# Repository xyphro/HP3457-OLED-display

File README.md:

# HP3457-OLED-display
A modern replacement for the low contrast HP3457 Multimeter LCD

HP3457 is a great multimeter of the pre Keysight and pre Agilent era from HP.
If you do some research on it, you get to learn a lot of details of how much nice engineering work has been put into the development of this multimeter. It is certainly one of the things, that was developed by great experienced engineers and is a masterpiece in finding proper solutions for technical challenges to push accuracy but also measurement speed on the right level.

HOWEVER: The display is crap. It is a low contrast display with small characters and extremly hard to read under most conditions. When I got mine, I rarely used it just for that reason.

I researched a bit on possible options and found 2 solutions:
- Mount a backlight behind the LCD. This is a very risky task, but I tried it out: The contrast gets even worse and actually it felt even like a downgrade of the display.
- A great sophisticated replacement LED display done by an EEVBlog user called "Xi": [https://www.eevblog.com/forum/projects/led-display-for-hp-3457a-multimeter-i-did-it-)](https://www.eevblog.com/forum/projects/led-display-for-hp-3457a-multimeter-i-did-it-)). Unfortunately this solution requires some difficult production techniques (milling LED displays to insert dots/comma leds, milling PCBs, ...).

I looked for solutions that were simpler to realize, such as matching TFT IPS panels, big OLED screens but failed to find a matching display.

After long thinking I had an idea... Let's use the cheapest OLED display that have very good availability: 0.87" i2c displays from Aliexpress. They are smaller than the required 10mm digit distance and just fit also mechanically into the display housing, without the need to cut pieces of the housing away.

To explain the idea - here 2 pictures:

# The final result:

This video shows my final solution to the problem:

(Well, not the most entertaining video in this world, but... It serves the job :-) )

# Building the display yourself:

This repositories contains sourcecode and hw design files in "raw" formats, but also the binary output.

I ordered the PCBs originally at JLCPCB. Both PCBs are located on a single panel and you can cut them in half after receiving them. The Gerber files are located under hardware/gerber.
In case you want to modify the PCB yourself, feel free to do so (but share it back) and use the files located under hardware/eagle to create your own design.

The software was created using Atmel Studio 7.0 and the project can be directly opened with it for editing if desired.

Don't forget to program the fuses of the ATMega8 MCU and select 8 MHz internal RC oscillator as clock source (otherwise it runs too slow with its default 1 MHz clock only).

NOTE: Ensure to buy the 0.87" variant of the OLEDS. There are also popular 0.91" variants available, but they are to wide! 
I bought my displays directly on Aliexpress: https://de.aliexpress.com/item/1005001856921229.html
In case the above link stops working, search for items like "XABL 0.87 Inch OLED"

I personally tested SSD1336 based display. EEVBlog User Miti bought a display with a CH1115 controller. This controller has a different command set. We jointly have added support for CH1115 displays to the code. In case you have such a SSD1336 you will need to rebuild the software with the `#define DISPLAYTYPE_CH1115` being enabled within oled.c. Otherwise the original SSD1336 based OLED displays will be supported.

The prebuilt binaries provided in this repository are built for SSD1336 based displays.

# Annuciators:

Annuciators are the small triangles / TEXT labels underneath the display. They are used to signal state information of the multimeter.

There are 3 different flavors realized. To select them when building the software, edit this define in annuciatorsel.h:
#define ANNUCIATORS_PERSONALITY HP3457_ICONS

And select any of the 3 below ones:

- HP3457_ORIGINAL - These are the small triangles, that rely on the information printed on the frontpanel underneath the display:

- HP3457_ICONS  - Small textual labels on the OLEDS itself:

- HP3478_ICONS - textual labels matching the HP3478 / 3468 display

The software/hex folder also contains precompiled .hex images for those 3 different annuciators versions.

# Putting it together

After soldering the PCBs and flashing the MCU, you can mount the PCB to your lovely HP3457 multimeter. The original press fit DIP socket can be directly plugged into the PCB.
The OLED display requires a second voltage source to power the OLEDs themselfes. This can be an AC supply, but I recommend for the HP3457 to use the 5V voltage regulator in TO220 housing and connect the AC lines to pin 1 and 2, which is 12 V.

The overall current consumption @12V supply is low and only about 30mA.

After mounting it looks like this from the internal side (the red supply header is unconnected here):

Enjoy your shiny new Display :-)

# Update 14th February 2025

## Experience after 3+ years

After 3 years of continuous use the Display still works very well. I have the feeling that the OLEDs got a tiny bit dimmer, but it is still tremendously better as the original LC-Display.

## Command coverage

Before this update (14th February 2025) only commands sent by HP3457a were supported. Though new commands were discovered, which triggered more searching for commands. 
I could find a few more and implemented it. See below table for an overview.

| Command code (12 bit HEX) | Command mnemonic | Implementation status / comment|
|--------------------|----------------------|----------------------|
|028 |	WRA12L   | Tested myself on HP3457a. |
|068 |	WRB12L   | Tested myself on HP3457a. |
|0a8 |	WRC12L   | Tested myself on HP3457a. |
|0e8 |	WRAB6L   | Tested with playback of eevblog user Kawal's logic analyzer recording.|
|128 |	WRABC4L  | Not tested with HP instrument, have sent the command manually.|
|168 |	WRAB6R   | Not tested with HP instrument, have sent the command manually.|
|1a8 |	WRABC4R  | Not tested with HP instrument, have sent the command manually.|
|1e8 |	WRA1L    | Not tested with HP instrument, have sent the command manually.|
|228 |	WRB1L    | Not tested with HP instrument, have sent the command manually.|
|268 |	WRC1L    | Not tested with HP instrument, have sent the command manually.|
|2a8 |	WRA1R    | Not tested with HP instrument, have sent the command manually.|
|2e8 |	WRB1R    | Not tested with HP instrument, have sent the command manually.|
|328 |	WRC1R    | Not tested with HP instrument, have sent the command manually.|
|368 |	WRAB1R   | Not tested with HP instrument, have sent the command manually.|
|3a8 |	WRABC1L  | Not tested with HP instrument, have sent the command manually.|
|3e8 |	WRABC1R  | Not tested with HP instrument, have sent the command manually.|
|230 |  DISOFF   | Implemented, but disabled. It results in wrong behavior on HP3457a. This command is supposed to turn the display OFF. It never gets sent on HP3457A.|
|320 |  DISTOG   | Implemented, but disabled. It results in wrong behavior on HP3457a. This command is supposed to turn the display OFF. It gets sent on HP3457A, BUT turns the display continously on and off. Before this command always command code 0x2E0 is sent and it is unknown what this command does.|
|3FC |  DISCMP   | Not implemented, because it is unknown what this command is supposed to do. It does not get sent by HP3457a.|
|3F0 | PERSCLT | Tested myself on HP3457a. Note that in previous FW versions it was not enabled.|
|2F0 | WRITAN  | Tested myself on HP3457a. Updates the annuciators.|
|2E0 | ??????  | Unknown command. It gets sent by HP3457a every time before the DISTOG command is sent.|

In case you have ANY information about the unknown HP LCD display commands let me know please. Or if you have a FW image of an original LCD display for analysis :-)

# Further links / Information

An eevblog thread on this project exists with lots of other users HW variant, experience and updates. E.g. HW variants can be found without isolator IC and using LDOs.

Have a look here: <a href="https://www.eevblog.com/forum/testgear/hp3548-hp3457-oled-display/" target="_blank">https://www.eevblog.com/forum/testgear/hp3548-hp3457-oled-display/</a>

In case you build the HW in this project note that it makes use of the 5V supply on the Display connector to supply the isolator IC. HP seems to put series resistors on the main PCB to limit the display IC current. You will very likely need to bridge these resistors - or build one of the eevblog variants with Isolator IC.

# Compatibility with other HP devices

The design might be compatible with other HP devices, but I personally only tested it with HP3547a. 
It is in the meantime confirmed, that the display works on HP3548 HP3478a and HP3852A too.

Chances are there that it might work for HP3468 and the HP66xx "tank" power supplies too. This is not tested by me (yet). If anybody is looking for adventures and tries this out, please feedback information to me, so that I can mark it is compatible here or share the required SW updates with a wider audience.

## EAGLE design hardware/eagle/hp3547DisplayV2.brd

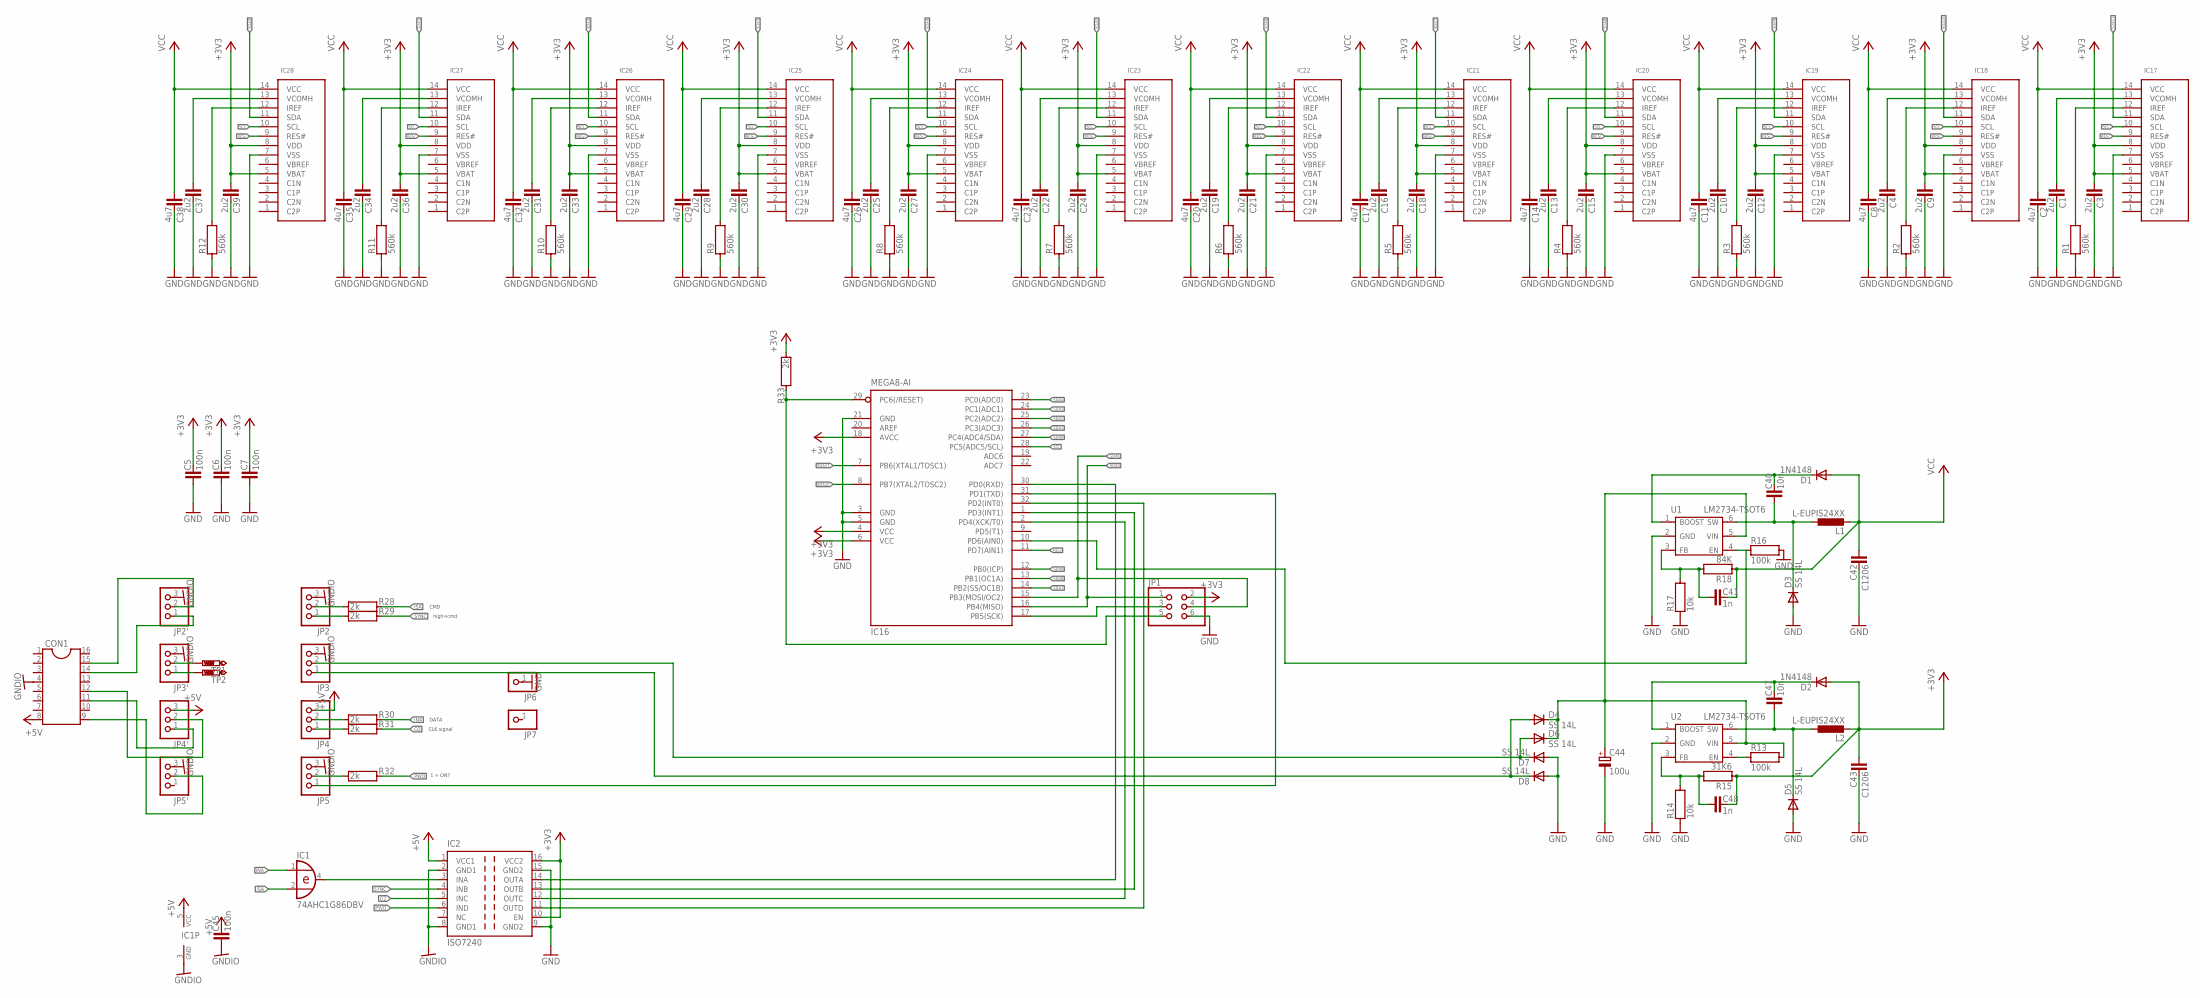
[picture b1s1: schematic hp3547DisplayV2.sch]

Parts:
C1, C3, C4, C9, C10, C12, C13, C15, C16, C18, C19, C21, C22, C24, C25, C27, C28, C30, C31, C33, C34, C36, C37, C39: 2u2; C0603
C2, C8, C11, C14, C17, C20, C23, C26, C29, C32, C35, C38: 4u7; C0805
C5, C6, C7, C45: 100n; C0603
C40, C47: 10n; C0603
C41, C48: 1n; C0603
C42, C43: C1206
C44: 100u; PANASONIC_E
CON1: DIL16BIGHOLE
D1, D2: 1N4148; DO214AC
D3, D4, D5, D6, D7, D8: SS 14L; SOD-123_MINI-SMA
IC1: 74AHC1G86DBV; SOT23-5
IC2: ISO7240; SO-16DW
IC16: MEGA8-AI; TQFP32-08
IC17, IC18, IC19, IC20, IC21, IC22, IC23, IC24, IC25, IC26, IC27, IC28: OLED0.87
JP1: PINHD-2X3; 2X03
JP2, JP2', JP3, JP3', JP4, JP4', JP5, JP5': PINHD-1X3; 1X03
JP6, JP7: PINHD-1X1; 1X01
L1, L2: L-EUPIS24XX; PIS24XX
R1, R2, R3, R4, R5, R6, R7, R8, R9, R10, R11, R12: 560k; R0402
R13, R16: 100k; R0603
R14, R17: 10k; R0603
R15: 31K6; R0603
R18: 84K; R0603
R28, R29, R30, R31, R32, R33: 2k; R0603
TP1, TP2: PTR1PAD1-13Y; P1-13Y
U1, U2: LM2734-TSOT6; TSOT6

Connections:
+3V3: C3.1, C5.2, C6.2, C7.2, C9.1, C12.1, C15.1, C18.1, C21.1, C24.1, C27.1, C30.1, C33.1, C36.1, C39.1, C43.1, C48.2, D2.A, IC2.10 (EN), IC2.16 (VCC2), IC16.4 (VCC), IC16.6 (VCC), IC16.18 (AVCC), IC17.5 (VBAT), IC17.8 (VDD), IC18.5 (VBAT), IC18.8 (VDD), IC19.5 (VBAT), IC19.8 (VDD), IC20.5 (VBAT), IC20.8 (VDD), IC21.5 (VBAT), IC21.8 (VDD), IC22.5 (VBAT), IC22.8 (VDD), IC23.5 (VBAT), IC23.8 (VDD), IC24.5 (VBAT), IC24.8 (VDD), IC25.5 (VBAT), IC25.8 (VDD), IC26.5 (VBAT), IC26.8 (VDD), IC27.5 (VBAT), IC27.8 (VDD), IC28.5 (VBAT), IC28.8 (VDD), JP1.2, L2.1 (2), R15.1, R33.2
+5V: C45.2, CON1.8, IC1.5 (VCC), IC2.1 (VCC1), JP4.3, JP4'.3
GND: C1.2, C2.2, C3.2, C4.2, C5.1, C6.1, C7.1, C8.2, C9.2, C10.2, C11.2, C12.2, C13.2, C14.2, C15.2, C16.2, C17.2, C18.2, C19.2, C20.2, C21.2, C22.2, C23.2, C24.2, C25.2, C26.2, C27.2, C28.2, C29.2, C30.2, C31.2, C32.2, C33.2, C34.2, C35.2, C36.2, C37.2, C38.2, C39.2, C42.2, C43.2, C44.-, D3.A, D5.A, D7.A, D8.A, IC2.9 (GND2), IC2.15 (GND2), IC16.3 (GND), IC16.5 (GND), IC16.21 (GND), IC17.7 (VSS), IC18.7 (VSS), IC19.7 (VSS), IC20.7 (VSS), IC21.7 (VSS), IC22.7 (VSS), IC23.7 (VSS), IC24.7 (VSS), IC25.7 (VSS), IC26.7 (VSS), IC27.7 (VSS), IC28.7 (VSS), JP1.6, JP6.1, R1.1, R2.1, R3.1, R4.1, R5.1, R6.1, R7.1, R8.1, R9.1, R10.1, R11.1, R12.1, R14.1, R16.2, R17.1, U1.2 (GND), U2.2 (GND)
GNDIO: C45.1, CON1.4, IC1.3 (GND), IC2.2 (GND1), IC2.8 (GND1), JP2.3, JP2'.3, JP3.3, JP3'.3, JP5.3, JP5'.3
INA: IC1.1 (I0), R30.1
ISA: IC1.2 (I1), R28.1
unnamed: IC18.12 (IREF), R2.2
unnamed: C4.1, IC18.13 (VCOMH)
unnamed: IC17.12 (IREF), R1.2
unnamed: C1.1, IC17.13 (VCOMH)
unnamed: JP2.2, R28.2
unnamed: IC19.12 (IREF), R3.2
unnamed: JP2.1, R29.2
unnamed: C10.1, IC19.13 (VCOMH)
unnamed: JP4.2, R30.2
unnamed: IC20.12 (IREF), R4.2
unnamed: C13.1, IC20.13 (VCOMH)
unnamed: JP4.1, R31.2
unnamed: IC21.12 (IREF), R5.2
unnamed: C16.1, IC21.13 (VCOMH)
unnamed: JP5.2, R32.2
unnamed: IC22.12 (IREF), R6.2
unnamed: C19.1, IC22.13 (VCOMH)
unnamed: C40.2, D1.C, U1.1 (BOOST)
unnamed: IC23.12 (IREF), R7.2
unnamed: C22.1, IC23.13 (VCOMH)
unnamed: C40.1, D3.C, L1.2 (1), U1.6 (SW)
unnamed: IC24.12 (IREF), R8.2
unnamed: C25.1, IC24.13 (VCOMH)
unnamed: C47.2, D2.C, U2.1 (BOOST)
unnamed: IC25.12 (IREF), R9.2
unnamed: C28.1, IC25.13 (VCOMH)
unnamed: C47.1, D5.C, L2.2 (1), U2.6 (SW)
unnamed: IC26.12 (IREF), R10.2
unnamed: C31.1, IC26.13 (VCOMH)
unnamed: C48.1, R14.2, R15.2, U2.3 (FB)
unnamed: IC27.12 (IREF), R11.2
unnamed: C34.1, IC27.13 (VCOMH)
unnamed: R13.1, U2.4 (EN)
unnamed: IC28.12 (IREF), R12.2
unnamed: C37.1, IC28.13 (VCOMH)
unnamed: IC16.31 (PD1(TXD)), JP5.1
unnamed: C41.1, R17.2, R18.2, U1.3 (FB)
unnamed: IC16.10 (PD6(AIN0)), R16.1, U1.4 (EN)
unnamed: JP3'.1, TP2.TP
unnamed: JP3'.2, TP1.TP
unnamed: D6.A, D7.C, JP3.2
unnamed: D4.A, D8.C, JP3.1
unnamed: IC2.14 (OUTA), IC16.30 (PD0(RXD))
unnamed: IC1.4 (O), IC2.3 (INA)
unnamed: IC2.12 (OUTC), IC16.2 (PD4(XCK/T0))
unnamed: IC2.13 (OUTB), IC16.1 (PD3(INT1))
unnamed: IC2.11 (OUTD), IC16.32 (PD2(INT0))
unnamed: IC16.29 (PC6(/RESET)), JP1.5, R33.1
unnamed: CON1.9, JP5'.2
unnamed: IC16.17 (PB5(SCK)), JP1.3
unnamed: CON1.11, JP4'.1
unnamed: CON1.12, JP4'.2
unnamed: CON1.14, JP2'.1
unnamed: CON1.15, JP2'.2
O2: IC2.5 (INC), R31.1
PWO: IC2.6 (IND), R32.1
RES/: IC16.11 (PD7(AIN1)), IC17.9 (RES#), IC18.9 (RES#), IC19.9 (RES#), IC20.9 (RES#), IC21.9 (RES#), IC22.9 (RES#), IC23.9 (RES#), IC24.9 (RES#), IC25.9 (RES#), IC26.9 (RES#), IC27.9 (RES#), IC28.9 (RES#)
SCL: IC16.28 (PC5(ADC5/SCL)), IC17.10 (SCL), IC18.10 (SCL), IC19.10 (SCL), IC20.10 (SCL), IC21.10 (SCL), IC22.10 (SCL), IC23.10 (SCL), IC24.10 (SCL), IC25.10 (SCL), IC26.10 (SCL), IC27.10 (SCL), IC28.10 (SCL)
SDA0: IC16.27 (PC4(ADC4/SDA)), IC28.11 (SDA)
SDA1: IC16.26 (PC3(ADC3)), IC27.11 (SDA)
SDA2: IC16.25 (PC2(ADC2)), IC26.11 (SDA)
SDA3: IC16.24 (PC1(ADC1)), IC25.11 (SDA)
SDA4: IC16.23 (PC0(ADC0)), IC24.11 (SDA)
SDA5: IC16.16 (PB4(MISO)), IC23.11 (SDA), JP1.1
SDA6: IC16.15 (PB3(MOSI/OC2)), IC22.11 (SDA), JP1.4
SDA7: IC16.14 (PB2(SS/OC1B)), IC21.11 (SDA)
SDA8: IC16.13 (PB1(OC1A)), IC20.11 (SDA)
SDA9: IC16.12 (PB0(ICP)), IC19.11 (SDA)
SDA10: IC16.8 (PB7(XTAL2/TOSC2)), IC18.11 (SDA)
SDA11: IC16.7 (PB6(XTAL1/TOSC1)), IC17.11 (SDA)
SYNC: IC2.4 (INB), R29.1
VCC: C2.1, C8.1, C11.1, C14.1, C17.1, C20.1, C23.1, C26.1, C29.1, C32.1, C35.1, C38.1, C41.2, C42.1, D1.A, IC17.14 (VCC), IC18.14 (VCC), IC19.14 (VCC), IC20.14 (VCC), IC21.14 (VCC), IC22.14 (VCC), IC23.14 (VCC), IC24.14 (VCC), IC25.14 (VCC), IC26.14 (VCC), IC27.14 (VCC), IC28.14 (VCC), L1.1 (2), R18.1
VIN: C44.+, D4.C, D6.C, R13.2, U1.5 (VIN), U2.5 (VIN)

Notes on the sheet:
CLK signal
DATA
CMD
high=cmd
1 = ON?

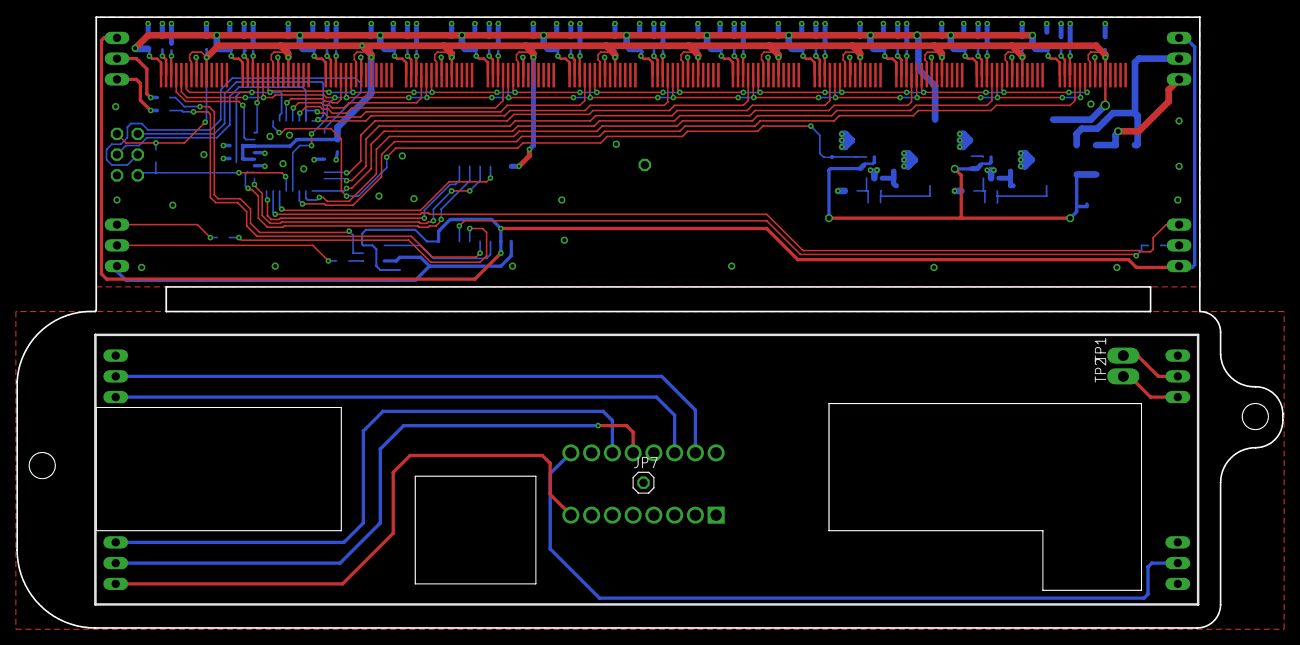
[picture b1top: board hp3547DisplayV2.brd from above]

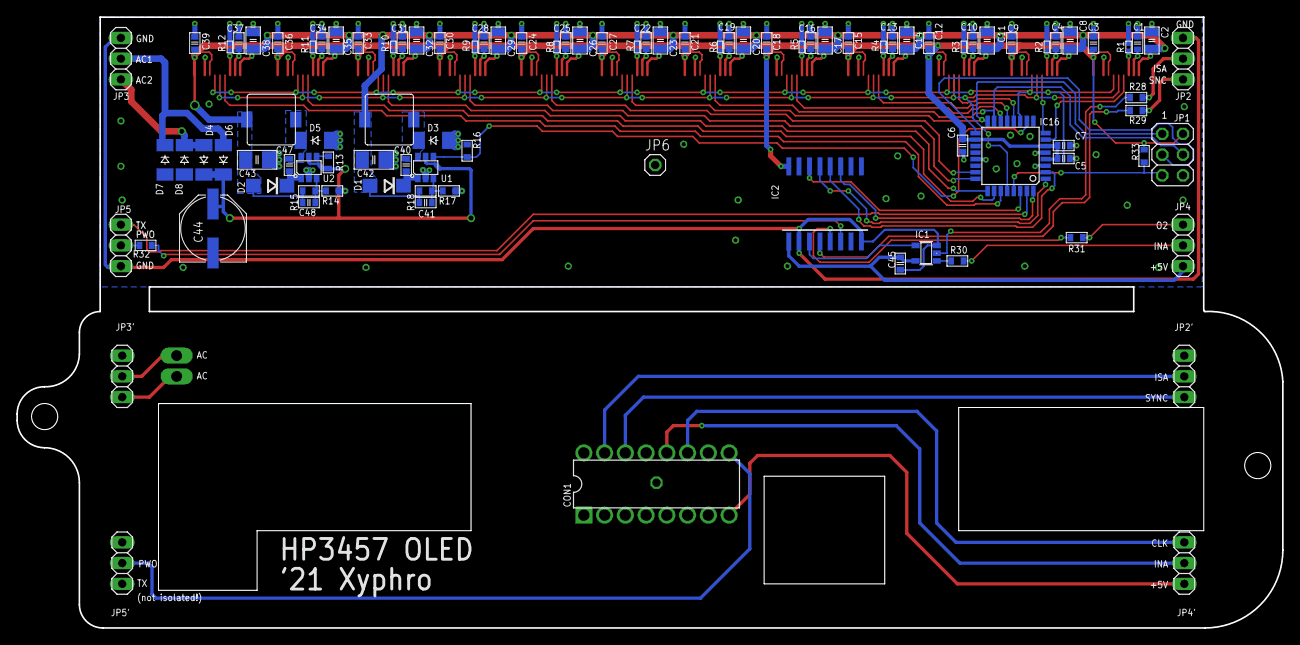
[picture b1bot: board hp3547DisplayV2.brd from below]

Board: 2 copper layers, 154.9 x 74.8 mm, 112 parts (97 on the bottom side), 79 nets.

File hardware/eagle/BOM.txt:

Qty Value        Device        Package          Parts                                                                                                              Description                                  MF MPN          OC_FARNELL OC_NEWARK TP_SIGNAL_NAME
1                DIL16BIGHOLE  DIL16BIGHOLE     CON1                                                                                                               Dual In Line / Socket                                                                           
2                PINHD-1X1     1X01             JP6, JP7                                                                                                           PIN HEADER                                                                                      
8                PINHD-1X3     1X03             JP2, JP2', JP3, JP3', JP4, JP4', JP5, JP5'                                                                         PIN HEADER                                                                                      
1                PINHD-2X3     2X03             JP1                                                                                                                PIN HEADER                                                                                      
2   100k         R0603         R0603            R13, R16                                                                                                                                                                                                           
4   100n         C0603         C0603            C5, C6, C7, C45                                                                                                                                                                                                    
1   100u         CPOL-EUE      PANASONIC_E      C44                                                                                                                POLARIZED CAPACITOR, European symbol                                                            
2   10k          R0603         R0603            R14, R17                                                                                                                                                                                                           
2   10n          C0603         C0603            C40, C47                                                                                                                                                                                                           
2   1N4148       DIODE-DO214AC DO214AC          D1, D2                                                                                                             DIODE                                                                                           
2   1n           C0603         C0603            C41, C48                                                                                                                                                                                                           
6   2k           R0603         R0603            R28, R29, R30, R31, R32, R33                                                                                                                                                                                       
24  2u2          C0603         C0603            C1, C3, C4, C9, C10, C12, C13, C15, C16, C18, C19, C21, C22, C24, C25, C27, C28, C30, C31, C33, C34, C36, C37, C39                                                                                                 
1   31K6         R0603         R0603            R15                                                                                                                                                                                                                
12  4u7          C0805         C0805            C2, C8, C11, C14, C17, C20, C23, C26, C29, C32, C35, C38                                                                                                                                                           
12  560k         R0402         R0402            R1, R2, R3, R4, R5, R6, R7, R8, R9, R10, R11, R12                                                                                                                                                                  
1   74AHC1G86DBV 74AHC1G86DBV  SOT23-5          IC1                                                                                                                2-input EXCLUSIV-OR gate                                                                        
1   84K          R0603         R0603            R18                                                                                                                                                                                                                
2   C1206        C1206         C1206            C42, C43                                                                                                                                                                                                           
1   ISO7240      ISO7240       SO-16DW          IC2                                                                                                                HIGH SPEED QUAD DIGITAL ISOLATORS               ISO7240MDW   1755124    58M0385                 
2   L-EUPIS24XX  L-EUPIS24XX   PIS24XX          L1, L2                                                                                                                                                                                                             
2   LM2734-TSOT6 LM2734-TSOT6  TSOT6            U1, U2                                                                                                             Thin SOT23 1A Load Step-Down DC-DC Regulator                                                    
1   MEGA8-AI     MEGA8-AI      TQFP32-08        IC16                                                                                                               MICROCONTROLLER                                 ATMEGA8-16AU 9171371    73M8863                 
12  OLED0.87     OLED0.87      OLED0.87         IC17, IC18, IC19, IC20, IC21, IC22, IC23, IC24, IC25, IC26, IC27, IC28                                                                                                                                             
2   PTR1PAD1-13Y PTR1PAD1-13Y  P1-13Y           TP1, TP2                                                                                                           TEST PIN                                                                                        
6   SS 14L       CGRM4001-G    SOD-123_MINI-SMA D3, D4, D5, D6, D7, D8                                                                                             Molded plasitc,JEDEC SOD-123/Mini SMA

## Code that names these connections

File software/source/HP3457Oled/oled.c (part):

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uint8_t oled_dots [12]; // dot content of all 12 digits

//************************************************************************
// PD7 = RESET
// PC5 = SCL
// PC4, PC3, PC2, PC1, PC0, PC7, PC6 = SDA0..6
// PB2, PB1, PB0, PB7, PB6           = SDA7..11
// PD6 = POWER (high active)
//
// Experimentally determined pixel range:
// line 30 = BOTTOM, line 127 = TOP => 98 pixels
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
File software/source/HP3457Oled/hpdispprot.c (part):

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
/***********************************************************************
 * Connection scheme:
 * PD0(RXD)    = INA ^ ISA (data) (Actually it would not be required to do a HW XOR, but here it helped to save 
 *                                 money for a 8 line isolator IC. In case you don't want galvanic isolation, you 
 *                                 could optimize the XOR IC away).
 * PD3(INT1)   = SYNC (high = command, low = data)
 * PD4(XCK/T0) = O2 (clock)
 * PD2(INT0)   = PWO (power up)
 **
 * Principle: 
 * The HP3457 sends datagrams that are command + data payload based.
 * The SYNC line identifies if the data is a command (SYNC = HIGH) or data (SYNC = LOW).
 * A command has a bitlength of 10 bits, the data payload is variable in length as function of the received command
 * 
 * PD3 is programmed to generate an interrupt on a rising edge (=start of a command).
 *   Once the interrupt arrives, To will be setup to generate an interrupt for every rising edge of the O2=clock line.
 * This timer interrupt does receive bits and store them for later processing.
 *
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#define	CMD_WRAB1R  (0xda) /* = 0xDA x4 = 0x368 = shift right 1 digit and write registers AB for 1 digit */
#define	CMD_WRABC1L (0xea) /* = 0xEA x4 = 0x3a8 = shift left 1 digit and write registers ABC for 1 digit */
#define	CMD_WRABC1R (0xfa) /* = 0xFA x4 = 0x3e8 = shift left 1 digit and write registers ABC for 1 digit */
#define	CMD_WRITAN  (0xbc) /* = 0xBC x4 = 0x2F0 = write the annunciators (eg the little arrows that are below the digits). The annunciators will follow in the data frame ("INA" line): there is one bit per annunciator, and the top right annunciator is transmitted first */

#define	CMD_DISOFF       (0x8C) /* = 0x8C x4 = 0x230 = Turn display off */
#define	CMD_DISTOG       (0xC8) /* = 0xC8 x4 = 0x320 = toggle the display ON/OFF (I don't know why this command is sent everytime (the sequence is always FC, B8, C8, BC, ...), maybe the unknow command B8 tells to switch the display OFF, then the C8 command swithes the display ON?) */
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
uint8_t cnt=0; // bitcounter for display command receiver

// PD3 interrupt - triggered on every rising edge of the PD3 pin 
ISR(INT1_vect)
{
	if (PIND & (1<<2))
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	PORTD &= ~( (1<<0) | (1<<3) | (1<<4) | (1<<2) ); // all pins = no pullup
	DDRD  &= ~( (1<<0) | (1<<3) | (1<<4) | (1<<2) ); // all pins = input
	
	// Enable rising edge interrupt on PD3 = SYNC
	MCUCR |= (3<<2); // trigger INT1 on rising edge
	GIFR  |= (1<<7); // Clear INT1 interrupt flag
	GICR  |= (1<<7); // enable INT1 (It will stay permanently enabled)
	
	// Setup Timer 0 (Used for clock detection)
	//TCCR0 =   (6<<1); // Clock on falling edge of O2 =PD4(T0) pin
	TCCR0 =   (0<<1); // Clock on falling edge of O2 =PD4(T0) pin
	TCNT0 = -3; // generate a timer interrupt after skipping 2 clock cycles
	TIFR |= (1<<0); // clear any pending interrupt
	TIMSK |= (1<<0); // enable timer0 overflow interrupt (an interrupt occurs when wraparround from 0xff to 0 happens)
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
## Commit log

2022-02-05 Initial commit of all files
2022-02-05 insert the correct photos
2022-02-05 fix typo
2022-02-05 "unmirror" the PDF schematic (Thanks Hexley!)
2022-02-05 Add conversion scripts for segment display and annuciator icons
2022-02-06 Show PowerConnection
2022-02-06 Added some details of the display
2022-02-08 Add BOM and component placement diagram
2023-04-14 Update README.md
    Line 85 - edited typo "HP3547" to "HP3457"
2025-02-14 Implement all 16 Display Character functions
    See upcoming README.MD
2025-02-14 Add information for the FW update
2025-02-15 Updated display reset timing
    The reset was so long, that commands from the supply were already sent and missed in the updates. Resulting e.g. in short phases of @@@@@@@@ being shown.
2025-03-01 Added support for CH1115 based OLED displays
    see readme.md for explanations.
